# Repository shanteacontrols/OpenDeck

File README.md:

# OpenDeck

OpenDeck is a platform for building interactive control and sensing devices using MIDI and OSC. From USB MIDI DJ controllers and DAW control surfaces to Ethernet-connected OSC nodes, sensor interfaces and media installations, OpenDeck supports a wide range of hardware projects.

The main platform features:

* Browser-based configuration
* No firmware development required
* Hardware-independent - supports multiple MCU families and development boards
* MIDI and OSC support
* Extensible sensor support

The platform lets you focus on hardware and interaction design rather than tweaking and debugging firmware.

*Click the image below for a demo video of the [OpenDeck configurator](https://config.shanteacontrols.com)*

Configurator is available either [online](https://config.shanteacontrols.com) or [offline](https://github.com/shanteacontrols/OpenDeckUI/releases).

*Some of the devices built with OpenDeck*

## Peripherals

OpenDeck supports the following peripherals:

### Core I/O

* Buttons
* Encoders
* Single-color LEDs and other types of outputs such as relays or transistors
* Potentiometers
* FSRs (force-sensitive resistors)

### Displays

* [Nextion HMI](https://nextion.tech/) touchscreen displays
* [SSD1306 small OLED display](https://www.adafruit.com/product/326)

### Sensors

* [APDS-9960 proximity, light, RGB, and gesture sensor](https://www.adafruit.com/product/3595) - OSC only
* [CAP1188 8-Key Capacitive Touch Sensor](https://www.adafruit.com/product/1602) - OSC only
* [VL53L4CX time of flight distance sensor](https://www.adafruit.com/product/5425) - OSC only
* [VL53L5CX 8x8 time of flight distance sensor](https://www.sparkfun.com/sparkfun-qwiic-tof-imager-vl53l5cx.html) - OSC only
* [BNO085 9-DOF orientation IMU fusion sensor](https://www.adafruit.com/product/4754) - OSC only

Each sensor has specific configuration options such as smoothing, selectable event output etc.

## Features

OpenDeck provides extensive MIDI and OSC functionality:

* MIDI: sending of both 7-bit and 14-bit Non-Registered Parameter Numbers (NRPN), latching messages on buttons, various encoding modes for quadrature encoders, output control using MIDI In, configurable MIDI channels for each component individually, Bluetooth MIDI and more.
* OSC: Ethernet transport, configurable destinations, sensor data streaming, output control, automatic network discovery via mDNS, network-based configuration and firmware updates.

A detailed guide to all supported configurable features can be found [here](https://github.com/shanteacontrols/OpenDeck/wiki/Configurable-features).

If the feature you want isn't supported yet, don't feel discouraged. Open up a [discussion thread](https://github.com/shanteacontrols/OpenDeck/discussions) and let's talk about it.

## Official board

Currently, there is only one official board available to buy: the L variant, where "L" stands for "large". The board is available on [Lectronz store](https://lectronz.com/products/opendeck-l/).

This board is based on Raspberry Pi RP2040 microcontroller and features the following:

* 128 digital inputs
* 64 digital outputs
* 64 analog inputs
* DIN MIDI
* USB MIDI (USB C)
* Connector for touchscreen
* Connector for I2C OLED display
* Additional connectors with 3V+GND and 5V+GND connections

The L board doesn't have OSC support. It focuses on providing lots of I/O specifically for USB and DIN MIDI use-cases. OSC functionality is available on a number of supported Ethernet-enabled boards.

## Supported boards

The firmware supports various other boards, both small and large:

| Board | MIDI | OSC |
| --- | --- | --- |
| [Adafruit Grand Central M4 Express](https://www.adafruit.com/product/4064) | USB, DIN | No |
| [Adafruit Metro ESP32-S3](https://www.adafruit.com/product/5500) | USB, DIN | No |
| [Adafruit Metro ESP32-S3](https://www.adafruit.com/product/5500) + [W5500 Ethernet Shield](https://wiznet.io/products/open-source-hardware/w5500-ethernet-shield) | USB | Ethernet |
| [Adafruit Metro ESP32-S3](https://www.adafruit.com/product/5500) + [W6100 Ethernet Shield](https://wiznet.io/products/open-source-hardware/w6100-ethernet-shield) | USB | Ethernet |
| [Adafruit Metro RP2040](https://www.adafruit.com/product/5786) | USB, DIN | No |
| [Adafruit Metro RP2040](https://www.adafruit.com/product/5786) + [W5500 Ethernet Shield](https://wiznet.io/products/open-source-hardware/w5500-ethernet-shield) | USB | Ethernet |
| [Adafruit Metro RP2040](https://www.adafruit.com/product/5786) + [W6100 Ethernet Shield](https://wiznet.io/products/open-source-hardware/w6100-ethernet-shield) | USB | Ethernet |
| [Arduino Nano 33 BLE](https://store.arduino.cc/products/arduino-nano-33-ble) | USB, DIN, BLE | No |
| [LILYGO T-ETH Elite](https://lilygo.cc/products/t-eth-elite-1) | USB | Ethernet |
| [nRF52840 DK](https://www.nordicsemi.com/Products/Development-hardware/nrf52840-dk) | USB, DIN, BLE | No |
| [nRF5340 DK](https://www.nordicsemi.com/Products/Development-hardware/nrf5340-dk) | USB, DIN, BLE | No |
| [Olimex ESP32-POE](https://www.olimex.com/Products/IoT/ESP32/ESP32-POE/open-source-hardware) | No | Ethernet |
| [Raspberry Pi Pico](https://www.raspberrypi.com/products/raspberry-pi-pico/) | USB, DIN | No |
| [Raspberry Pi Pico 2](https://www.raspberrypi.com/products/raspberry-pi-pico-2/) | USB, DIN | No |
| [ST Discovery F407VG](https://www.st.com/en/evaluation-tools/stm32f4discovery.html) | USB, DIN | No |
| [ST Nucleo F767ZI](https://www.st.com/en/evaluation-tools/nucleo-f767zi.html) | DIN | Ethernet |
| [ST Nucleo H563ZI](https://www.st.com/en/evaluation-tools/nucleo-h563zi.html) | DIN | Ethernet |
| [ST Nucleo H753ZI](https://www.st.com/en/evaluation-tools/nucleo-h753zi.html) | DIN | Ethernet |
| [STM32F411 Black Pill V3+](https://www.adafruit.com/product/4877) with populated external flash | USB, DIN | No |
| [Teensy 4.0](https://www.pjrc.com/store/teensy40.html) | USB, DIN | No |
| [Teensy 4.1](https://www.pjrc.com/store/teensy41.html) | USB, DIN | No |
| [Waveshare Core405R](https://www.waveshare.com/core405r.htm) | USB, DIN | No |
| [Waveshare ESP32-S3-ETH](https://www.waveshare.com/esp32-s3-eth.htm) | USB | Ethernet |
| [W5500-EVB-Pico](https://docs.wiznet.io/Product/Open-Source-Hardware/w5500-evb-pico) | USB | Ethernet |
| [W5500-EVB-Pico2](https://docs.wiznet.io/Product/Open-Source-Hardware/w5500-evb-pico2) | USB, DIN | Ethernet |
| [W6100-EVB-Pico](https://docs.wiznet.io/Product/Open-Source-Hardware/w6100-evb-pico) | USB, DIN | Ethernet |
| [W6100-EVB-Pico2](https://docs.wiznet.io/Product/Open-Source-Hardware/w6100-evb-pico2) | USB, DIN | Ethernet |
| [wESP32](https://wesp32.com/) | No | Ethernet |

For more details on supported boards, check the [wiki page](https://github.com/shanteacontrols/OpenDeck/wiki). Support for custom boards [can also be added](https://github.com/shanteacontrols/OpenDeck/wiki/Creating-custom-board-variant).

## Documentation

Available on dedicated [Wiki section](https://github.com/shanteacontrols/OpenDeck/wiki/).

## Discussion

Need help? Want to show off your OpenDeck-based builds? Head over to [Discussions](https://github.com/shanteacontrols/OpenDeck/discussions)!

## License

OpenDeck source code is available under Apache License v2.0. Zephyr RTOS, which OpenDeck is built on top of, is also licensed under Apache License v2.0.

Third-party components with different licenses:

* `u8g2`: Two-clause BSD
* `vl53l4cx`: Three-clause BSD
* `vl53l5cx`: Three-clause BSD
* `zlibs`: MIT

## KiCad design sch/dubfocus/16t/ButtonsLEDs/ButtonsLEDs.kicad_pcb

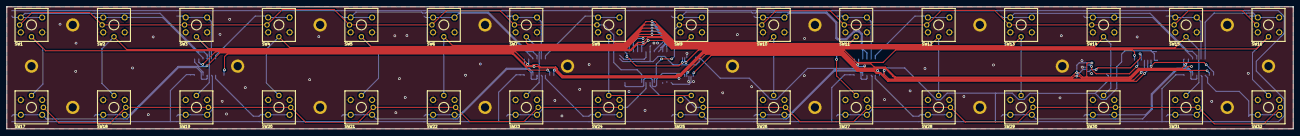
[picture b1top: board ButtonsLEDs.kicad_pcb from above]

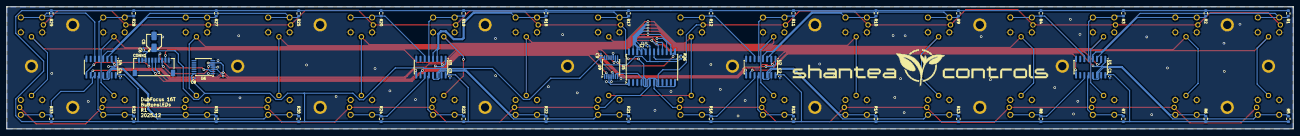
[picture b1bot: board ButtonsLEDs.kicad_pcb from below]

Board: 2 copper layers, 390.0 x 37.0 mm, 100 parts (50 on the bottom side), 61 nets.

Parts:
C1, C2, C3, C4, C6, C7, C8, C9: 100n; C_0402_1005Metric
C5: 10u; CP_Elec_4x5.4
CONN1: CONN_SM10B-SRSS-TB_JST
H1, H2, H3, H4, H5, H6, H7, H8, H9, H10, H11, H12, H13, H14, H15, H16, H17, H18: MountingHole_Pad; MountingHole_2.5mm_Pad
R1, R2, R3, R4, R5, R6, R7, R8, R9, R10, R11, R12, R13, R14, R15, R16, R17, R18, R19, R20, R21, R22, R23, R24, R25, R27, R28, R29, R30, R31, R32, R33: 4k7; R_0603_1608Metric
R26: 10k; R_0402_1005Metric
SW1, SW2, SW3, SW4, SW5, SW6, SW7, SW8, SW9, SW10, SW11, SW12, SW13, SW14, SW15, SW16, SW17, SW18, SW19, SW20, SW21, SW22, SW23, SW24, SW25, SW26, SW27, SW28, SW29, SW30, SW31, SW32: Omron-B3W-9
U1, U2, U3, U4: 74HC165; SOIC-16_3.9x9.9mm_P1.27mm
U5: MAX7219; SOIC-24W_7.5x15.4mm_P1.27mm
U6, U9: 74HCT125; TSSOP-14_4.4x5mm_P0.65mm

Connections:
+5V: C1.1, C2.1, C3.1, C4.1, C5.1, C6.1, C7.2, C8.2, C9.2, CONN1.2, CONN1.3, R1.2, R2.2, R3.2, R4.2, R5.2, R6.2, R7.2, R8.2, R9.2, R10.2, R11.2, R12.2, R13.2, R14.2, R15.2, R16.2, R17.2, R18.2, R19.2, R20.2, R21.2, R22.2, R23.2, R24.2, R25.2, R26.1, R27.2, R28.2, R29.2, R30.2, R31.2, R32.2, R33.2, U1.16 (VCC), U2.16 (VCC), U3.16 (VCC), U4.16 (VCC), U5.19 (V+), U6.14 (VCC), U9.14 (VCC)
/Buttons 1/BUTTON1: R1.1, SW1.1, SW1.2, U1.4 (D5)
/Buttons 1/BUTTON2: R2.1, SW2.1, SW2.2, U1.3 (D4)
/Buttons 1/BUTTON3: R3.1, SW3.1, SW3.2, U1.5 (D6)
/Buttons 1/BUTTON4: R4.1, SW4.1, SW4.2, U1.6 (D7)
/Buttons 1/BUTTON5: R5.1, SW17.1, SW17.2, U1.13 (D2)
/Buttons 1/BUTTON6: R6.1, SW18.1, SW18.2, U1.14 (D3)
/Buttons 1/BUTTON7: R7.1, SW19.1, SW19.2, U1.12 (D1)
/Buttons 1/BUTTON8: R8.1, SW20.1, SW20.2, U1.11 (D0)
/Buttons 2/BUTTON1: R9.1, SW5.1, SW5.2, U2.4 (D5)
/Buttons 2/BUTTON2: R10.1, SW6.1, SW6.2, U2.3 (D4)
/Buttons 2/BUTTON3: R11.1, SW7.1, SW7.2, U2.5 (D6)
/Buttons 2/BUTTON4: R12.1, SW8.1, SW8.2, U2.6 (D7)
/Buttons 2/BUTTON5: R13.1, SW21.1, SW21.2, U2.13 (D2)
/Buttons 2/BUTTON6: R14.1, SW22.1, SW22.2, U2.14 (D3)
/Buttons 2/BUTTON7: R15.1, SW23.1, SW23.2, U2.12 (D1)
/Buttons 2/BUTTON8: R16.1, SW24.1, SW24.2, U2.11 (D0)
/Buttons 3/BUTTON1: R17.1, SW9.1, SW9.2, U3.4 (D5)
/Buttons 3/BUTTON2: R18.1, SW10.1, SW10.2, U3.3 (D4)
/Buttons 3/BUTTON3: R19.1, SW11.1, SW11.2, U3.5 (D6)
/Buttons 3/BUTTON4: R20.1, SW12.1, SW12.2, U3.6 (D7)
/Buttons 3/BUTTON5: R21.1, SW25.1, SW25.2, U3.13 (D2)
/Buttons 3/BUTTON6: R22.1, SW26.1, SW26.2, U3.14 (D3)
/Buttons 3/BUTTON7: R23.1, SW27.1, SW27.2, U3.12 (D1)
/Buttons 3/BUTTON8: R24.1, SW28.1, SW28.2, U3.11 (D0)
/Buttons 4/BUTTON1: R25.1, SW13.1, SW13.2, U4.4 (D5)
/Buttons 4/BUTTON2: R27.1, SW14.1, SW14.2, U4.3 (D4)
/Buttons 4/BUTTON3: R28.1, SW15.1, SW15.2, U4.5 (D6)
/Buttons 4/BUTTON4: R29.1, SW16.1, SW16.2, U4.6 (D7)
/Buttons 4/BUTTON5: R30.1, SW29.1, SW29.2, U4.13 (D2)
/Buttons 4/BUTTON6: R31.1, SW30.1, SW30.2, U4.14 (D3)
/Buttons 4/BUTTON7: R32.1, SW31.1, SW31.2, U4.12 (D1)
/Buttons 4/BUTTON8: R33.1, SW32.1, SW32.2, U4.11 (D0)
/LEDs/LED_COLUMN_1: SW1.- (K), SW2.- (K), SW3.- (K), SW4.- (K), SW5.- (K), SW6.- (K), SW7.- (K), SW8.- (K), U5.8 (DIG_7)
/LEDs/LED_COLUMN_2: SW17.- (K), SW18.- (K), SW19.- (K), SW20.- (K), SW21.- (K), SW22.- (K), SW23.- (K), SW24.- (K), U5.7 (DIG_3)
/LEDs/LED_COLUMN_3: SW9.- (K), SW10.- (K), SW11.- (K), SW12.- (K), SW13.- (K), SW14.- (K), SW15.- (K), SW16.- (K), U5.5 (DIG_6)
/LEDs/LED_COLUMN_4: SW25.- (K), SW26.- (K), SW27.- (K), SW28.- (K), SW29.- (K), SW30.- (K), SW31.- (K), SW32.- (K), U5.6 (DIG_2)
/LEDs/LED_ROW_1: SW1.+ (A), SW16.+ (A), SW17.+ (A), SW32.+ (A), U5.17 (SEG_G)
/LEDs/LED_ROW_2: SW2.+ (A), SW15.+ (A), SW18.+ (A), SW31.+ (A), U5.16 (SEG_B)
/LEDs/LED_ROW_3: SW3.+ (A), SW14.+ (A), SW19.+ (A), SW30.+ (A), U5.15 (SEG_F)
/LEDs/LED_ROW_4: SW4.+ (A), SW13.+ (A), SW20.+ (A), SW29.+ (A), U5.14 (SEG_A)
/LEDs/LED_ROW_5: SW5.+ (A), SW12.+ (A), SW21.+ (A), SW28.+ (A), U5.20 (SEG_C)
/LEDs/LED_ROW_6: SW6.+ (A), SW11.+ (A), SW22.+ (A), SW27.+ (A), U5.21 (SEG_E)
/LEDs/LED_ROW_7: SW7.+ (A), SW10.+ (A), SW23.+ (A), SW26.+ (A), U5.22 (SEG_DP)
/LEDs/LED_ROW_8: SW8.+ (A), SW9.+ (A), SW24.+ (A), SW25.+ (A), U5.23 (SEG_D)
/MAX7219_CLK_3V: CONN1.9, U9.9 (3A)
/MAX7219_CLK_5V: U5.13 (CLK), U9.8 (3Y)
/MAX7219_DIN_3V: CONN1.5, U9.2 (1A)
/MAX7219_DIN_5V: U5.1 (DIN), U9.3 (1Y)
/MAX7219_LOAD_3V: CONN1.6, U9.5 (2A)
/MAX7219_LOAD_5V: U5.12 (LOAD), U9.6 (2Y)
/SR_IN_CLOCK_3V: CONN1.8, U6.5 (2A)
/SR_IN_CLOCK_5V: U1.2 (CP), U2.2 (CP), U3.2 (CP), U4.2 (CP), U6.6 (2Y)
/SR_IN_DAISY_OUT_1: U3.9 (Q7), U4.10 (DS)
/SR_IN_DAISY_OUT_2: U2.9 (Q7), U3.10 (DS)
/SR_IN_DAISY_OUT_3: U1.9 (Q7), U2.10 (DS)
/SR_IN_DATA: CONN1.4, U4.9 (Q7)
/SR_IN_LATCH_3V: CONN1.7, U6.2 (1A)
/SR_IN_LATCH_5V: U1.1 (~PL), U2.1 (~PL), U3.1 (~PL), U4.1 (~PL), U6.3 (1Y)
GND: C1.2, C2.2, C3.2, C4.2, C5.2, C6.2, C7.1, C8.1, C9.1, CONN1.1, CONN1.10, CONN1.S1, CONN1.S2, H1.1, H2.1, H3.1, H4.1, H5.1, H6.1, H7.1, H8.1, H9.1, H10.1, H11.1, H12.1, H13.1, H14.1, H15.1, H16.1, H17.1, H18.1, SW1.3, SW1.4, SW2.3, SW2.4, SW3.3, SW3.4, SW4.3, SW4.4, SW5.3, SW5.4, SW6.3, SW6.4, SW7.3, SW7.4, SW8.3, SW8.4, SW9.3, SW9.4, SW10.3, SW10.4, SW11.3, SW11.4, SW12.3, SW12.4, SW13.3, SW13.4, SW14.3, SW14.4, SW15.3, SW15.4, SW16.3, SW16.4, SW17.3, SW17.4, SW18.3, SW18.4, SW19.3, SW19.4, SW20.3, SW20.4, SW21.3, SW21.4, SW22.3, SW22.4, SW23.3, SW23.4, SW24.3, SW24.4, SW25.3, SW25.4, SW26.3, SW26.4, SW27.3, SW27.4, SW28.3, SW28.4, SW29.3, SW29.4, SW30.3, SW30.4, SW31.3, SW31.4, SW32.3, SW32.4, U1.8 (GND), U1.15 (~CE), U2.8 (GND), U2.15 (~CE), U3.8 (GND), U3.15 (~CE), U4.8 (GND), U4.15 (~CE), U5.4 (GND), U5.9 (GND), U6.1 (1~OE), U6.4 (2~OE), U6.7 (GND), U9.1 (1~OE), U9.4 (2~OE), U9.7 (GND), U9.10 (3~OE)
unnamed: R26.2, U5.18 (ISET)

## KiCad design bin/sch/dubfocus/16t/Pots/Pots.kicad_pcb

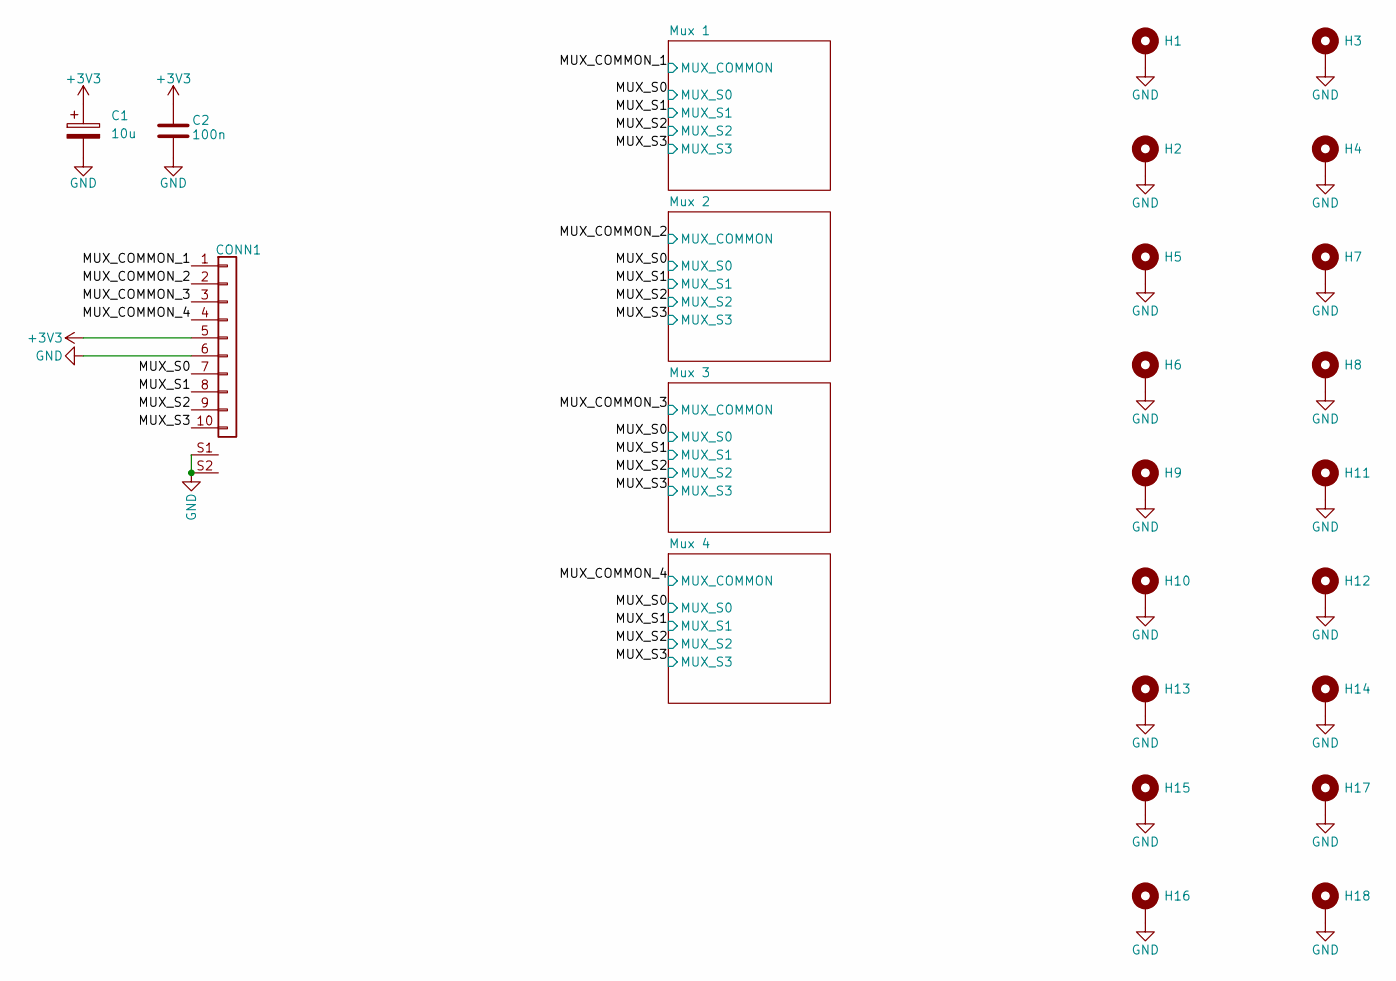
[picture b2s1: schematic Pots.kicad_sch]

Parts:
C1: 10u; CP_Elec_4x5.4; LCSC C4747968
C2: 100n; C_0402_1005Metric; LCSC C1525
CONN1: CONN_SM10B-SRSS-TB_JST; LCSC C160409
H1, H2, H3, H4, H5, H6, H7, H8, H9, H10, H11, H12, H13, H14, H15, H16, H17, H18: MountingHole_Pad; MountingHole_2.5mm_Pad

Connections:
+3V3: C1.1, C2.1, CONN1.5; also elsewhere on the board
/MUX_COMMON_1: CONN1.1; also elsewhere on the board
/MUX_COMMON_2: CONN1.2; also elsewhere on the board
/MUX_COMMON_3: CONN1.3; also elsewhere on the board
/MUX_COMMON_4: CONN1.4; also elsewhere on the board
/MUX_S0: CONN1.7; also elsewhere on the board
/MUX_S1: CONN1.8; also elsewhere on the board
/MUX_S2: CONN1.9; also elsewhere on the board
/MUX_S3: CONN1.10; also elsewhere on the board
GND: C1.2, C2.2, CONN1.6, CONN1.S1, CONN1.S2, H1.1, H2.1, H3.1, H4.1, H5.1, H6.1, H7.1, H8.1, H9.1, H10.1, H11.1, H12.1, H13.1, H14.1, H15.1, H16.1, H17.1, H18.1; also elsewhere on the board

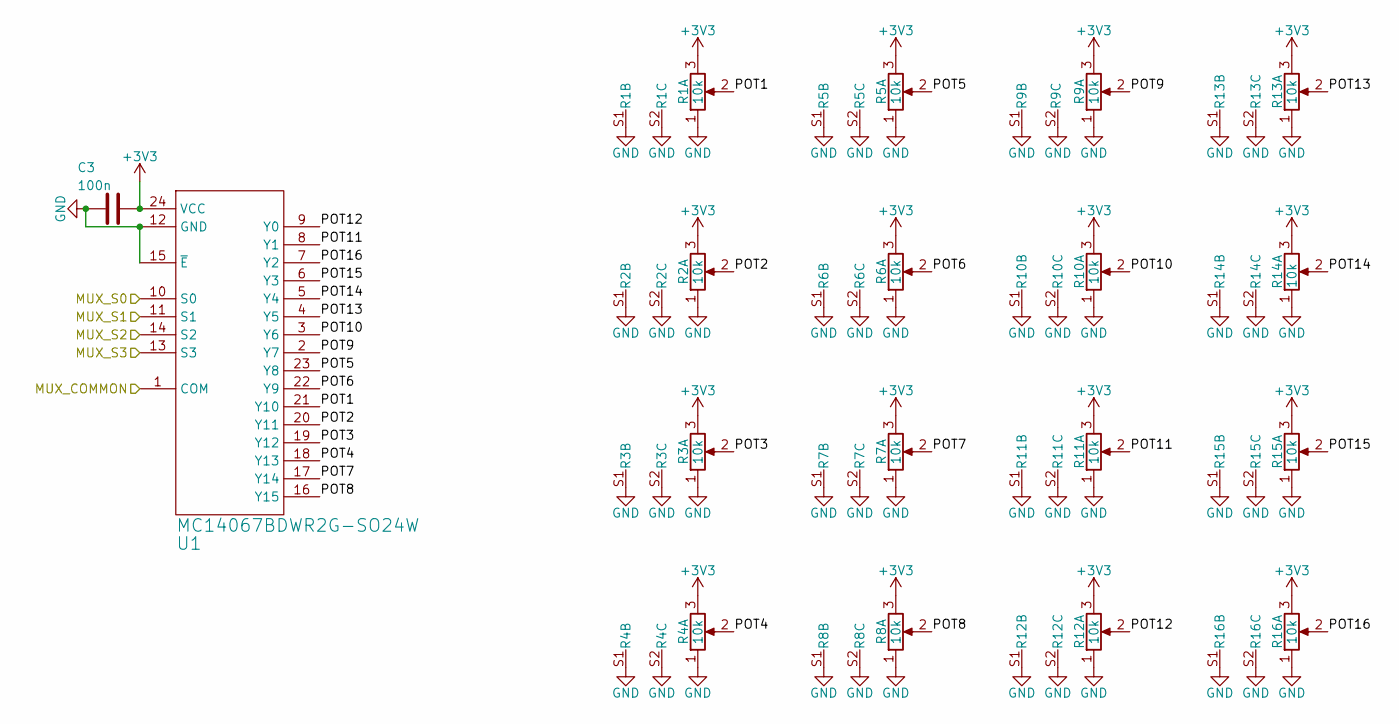
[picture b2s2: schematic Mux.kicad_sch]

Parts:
C3: 100n; C_0402_1005Metric; LCSC C1525
R1, R2, R3, R4, R5, R6, R7, R8, R9, R10, R11, R12, R13, R14, R15, R16: 10k; PTV09A-4025F-B103; LCSC C7262626
U1: MC14067BDWR2G-SO24W; SOIC-24W_7.5x15.4mm_P1.27mm; LCSC C555478

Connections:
+3V3: C3.2, R1.3, R2.3, R3.3, R4.3, R5.3, R6.3, R7.3, R8.3, R9.3, R10.3, R11.3, R12.3, R13.3, R14.3, R15.3, R16.3, U1.24 (VCC); also elsewhere on the board
/MUX_COMMON_1: U1.1 (COM); also elsewhere on the board
/MUX_S0: U1.10 (S0); also elsewhere on the board
/MUX_S1: U1.11 (S1); also elsewhere on the board
/MUX_S2: U1.14 (S2); also elsewhere on the board
/MUX_S3: U1.13 (S3); also elsewhere on the board
/Mux 1/POT1: R1.2, U1.21 (Y10)
/Mux 1/POT2: R2.2, U1.20 (Y11)
/Mux 1/POT3: R3.2, U1.19 (Y12)
/Mux 1/POT4: R4.2, U1.18 (Y13)
/Mux 1/POT5: R5.2, U1.23 (Y8)
/Mux 1/POT6: R6.2, U1.22 (Y9)
/Mux 1/POT7: R7.2, U1.17 (Y14)
/Mux 1/POT8: R8.2, U1.16 (Y15)
/Mux 1/POT9: R9.2, U1.2 (Y7)
/Mux 1/POT10: R10.2, U1.3 (Y6)
/Mux 1/POT11: R11.2, U1.8 (Y1)
/Mux 1/POT12: R12.2, U1.9 (Y0)
/Mux 1/POT13: R13.2, U1.4 (Y5)
/Mux 1/POT14: R14.2, U1.5 (Y4)
/Mux 1/POT15: R15.2, U1.6 (Y3)
/Mux 1/POT16: R16.2, U1.7 (Y2)
GND: C3.1, R1.1, R1.S1, R1.S2, R2.1, R2.S1, R2.S2, R3.1, R3.S1, R3.S2, R4.1, R4.S1, R4.S2, R5.1, R5.S1, R5.S2, R6.1, R6.S1, R6.S2, R7.1, R7.S1, R7.S2, R8.1, R8.S1, R8.S2, R9.1, R9.S1, R9.S2, R10.1, R10.S1, R10.S2, R11.1, R11.S1, R11.S2, R12.1, R12.S1, R12.S2, R13.1, R13.S1, R13.S2, R14.1, R14.S1, R14.S2, R15.1, R15.S1, R15.S2, R16.1, R16.S1, R16.S2, U1.12 (GND), U1.15 (~E); also elsewhere on the board

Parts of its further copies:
C4, C5, C6: 100n; C_0402_1005Metric; LCSC C1525
R17, R18, R19, R20, R21, R22, R23, R24, R25, R26, R27, R28, R29, R30, R31, R32, R33, R34, R35, R36, R37, R38, R39, R40, R41, R42, R43, R44, R45, R46, R47, R48, R49, R50, R51, R52, R53, R54, R55, R56, R57, R58, R59, R60, R61, R62, R63, R64: 10k; PTV09A-4025F-B103; LCSC C7262626
U2, U3, U4: MC14067BDWR2G-SO24W; SOIC-24W_7.5x15.4mm_P1.27mm; LCSC C555478

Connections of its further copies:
+3V3: C4.2, C5.2, C6.2, R17.3, R18.3, R19.3, R20.3, R21.3, R22.3, R23.3, R24.3, R25.3, R26.3, R27.3, R28.3, R29.3, R30.3, R31.3, R32.3, R33.3, R34.3, R35.3, R36.3, R37.3, R38.3, R39.3, R40.3, R41.3, R42.3, R43.3, R44.3, R45.3, R46.3, R47.3, R48.3, R49.3, R50.3, R51.3, R52.3, R53.3, R54.3, R55.3, R56.3, R57.3, R58.3, R59.3, R60.3, R61.3, R62.3, R63.3, R64.3, U2.24 (VCC), U3.24 (VCC), U4.24 (VCC); also elsewhere on the board
/MUX_COMMON_2: U2.1 (COM); also elsewhere on the board
/MUX_COMMON_3: U3.1 (COM); also elsewhere on the board
/MUX_COMMON_4: U4.1 (COM); also elsewhere on the board
/MUX_S0: U2.10 (S0), U3.10 (S0), U4.10 (S0); also elsewhere on the board
/MUX_S1: U2.11 (S1), U3.11 (S1), U4.11 (S1); also elsewhere on the board
/MUX_S2: U2.14 (S2), U3.14 (S2), U4.14 (S2); also elsewhere on the board
/MUX_S3: U2.13 (S3), U3.13 (S3), U4.13 (S3); also elsewhere on the board
/Mux 2/POT1: R17.2, U2.21 (Y10)
/Mux 2/POT2: R18.2, U2.20 (Y11)
/Mux 2/POT3: R19.2, U2.19 (Y12)
/Mux 2/POT4: R20.2, U2.18 (Y13)
/Mux 2/POT5: R21.2, U2.23 (Y8)
/Mux 2/POT6: R22.2, U2.22 (Y9)
/Mux 2/POT7: R23.2, U2.17 (Y14)
/Mux 2/POT8: R24.2, U2.16 (Y15)
/Mux 2/POT9: R25.2, U2.2 (Y7)
/Mux 2/POT10: R26.2, U2.3 (Y6)
/Mux 2/POT11: R27.2, U2.8 (Y1)
/Mux 2/POT12: R28.2, U2.9 (Y0)
/Mux 2/POT13: R29.2, U2.4 (Y5)
/Mux 2/POT14: R30.2, U2.5 (Y4)
/Mux 2/POT15: R31.2, U2.6 (Y3)
/Mux 2/POT16: R32.2, U2.7 (Y2)
/Mux 3/POT1: R33.2, U3.21 (Y10)
/Mux 3/POT2: R34.2, U3.20 (Y11)
/Mux 3/POT3: R35.2, U3.19 (Y12)
/Mux 3/POT4: R36.2, U3.18 (Y13)
/Mux 3/POT5: R37.2, U3.23 (Y8)
/Mux 3/POT6: R38.2, U3.22 (Y9)
/Mux 3/POT7: R39.2, U3.17 (Y14)
/Mux 3/POT8: R40.2, U3.16 (Y15)
/Mux 3/POT9: R41.2, U3.2 (Y7)
/Mux 3/POT10: R42.2, U3.3 (Y6)
/Mux 3/POT11: R43.2, U3.8 (Y1)
/Mux 3/POT12: R44.2, U3.9 (Y0)
/Mux 3/POT13: R45.2, U3.4 (Y5)
/Mux 3/POT14: R46.2, U3.5 (Y4)
/Mux 3/POT15: R47.2, U3.6 (Y3)
/Mux 3/POT16: R48.2, U3.7 (Y2)
/Mux 4/POT1: R49.2, U4.21 (Y10)
/Mux 4/POT2: R50.2, U4.20 (Y11)
/Mux 4/POT3: R51.2, U4.19 (Y12)
/Mux 4/POT4: R52.2, U4.18 (Y13)
/Mux 4/POT5: R53.2, U4.23 (Y8)
/Mux 4/POT6: R54.2, U4.22 (Y9)
/Mux 4/POT7: R55.2, U4.17 (Y14)
/Mux 4/POT8: R56.2, U4.16 (Y15)
/Mux 4/POT9: R57.2, U4.2 (Y7)
/Mux 4/POT10: R58.2, U4.3 (Y6)
/Mux 4/POT11: R59.2, U4.8 (Y1)
/Mux 4/POT12: R60.2, U4.9 (Y0)
/Mux 4/POT13: R61.2, U4.4 (Y5)
/Mux 4/POT14: R62.2, U4.5 (Y4)
/Mux 4/POT15: R63.2, U4.6 (Y3)
/Mux 4/POT16: R64.2, U4.7 (Y2)
GND: C4.1, C5.1, C6.1, R17.1, R17.S1, R17.S2, R18.1, R18.S1, R18.S2, R19.1, R19.S1, R19.S2, R20.1, R20.S1, R20.S2, R21.1, R21.S1, R21.S2, R22.1, R22.S1, R22.S2, R23.1, R23.S1, R23.S2, R24.1, R24.S1, R24.S2, R25.1, R25.S1, R25.S2, R26.1, R26.S1, R26.S2, R27.1, R27.S1, R27.S2, R28.1, R28.S1, R28.S2, R29.1, R29.S1, R29.S2, R30.1, R30.S1, R30.S2, R31.1, R31.S1, R31.S2, R32.1, R32.S1, R32.S2, R33.1, R33.S1, R33.S2, R34.1, R34.S1, R34.S2, R35.1, R35.S1, R35.S2, R36.1, R36.S1, R36.S2, R37.1, R37.S1, R37.S2, R38.1, R38.S1, R38.S2, R39.1, R39.S1, R39.S2, R40.1, R40.S1, R40.S2, R41.1, R41.S1, R41.S2, R42.1, R42.S1, R42.S2, R43.1, R43.S1, R43.S2, R44.1, R44.S1, R44.S2, R45.1, R45.S1, R45.S2, R46.1, R46.S1, R46.S2, R47.1, R47.S1, R47.S2, R48.1, R48.S1, R48.S2, R49.1, R49.S1, R49.S2, R50.1, R50.S1, R50.S2, R51.1, R51.S1, R51.S2, R52.1, R52.S1, R52.S2, R53.1, R53.S1, R53.S2, R54.1, R54.S1, R54.S2, R55.1, R55.S1, R55.S2, R56.1, R56.S1, R56.S2, R57.1, R57.S1, R57.S2, R58.1, R58.S1, R58.S2, R59.1, R59.S1, R59.S2, R60.1, R60.S1, R60.S2, R61.1, R61.S1, R61.S2, R62.1, R62.S1, R62.S2, R63.1, R63.S1, R63.S2, R64.1, R64.S1, R64.S2, U2.12 (GND), U2.15 (~E), U3.12 (GND), U3.15 (~E), U4.12 (GND), U4.15 (~E); also elsewhere on the board

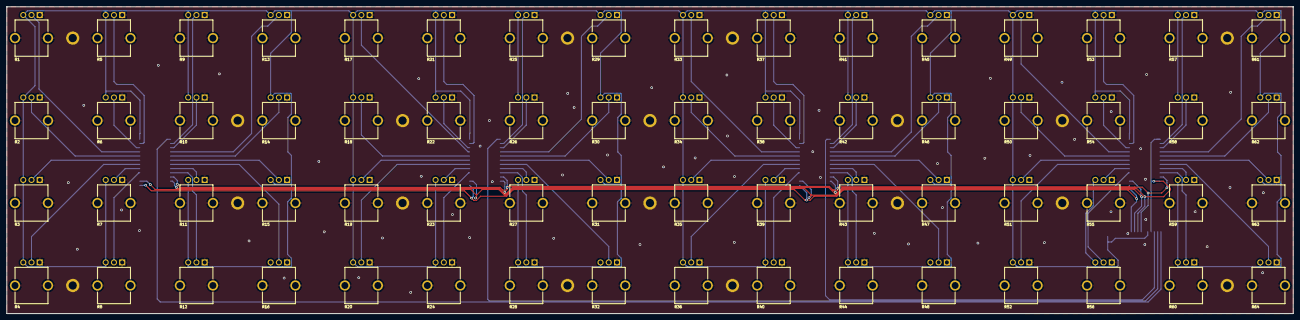
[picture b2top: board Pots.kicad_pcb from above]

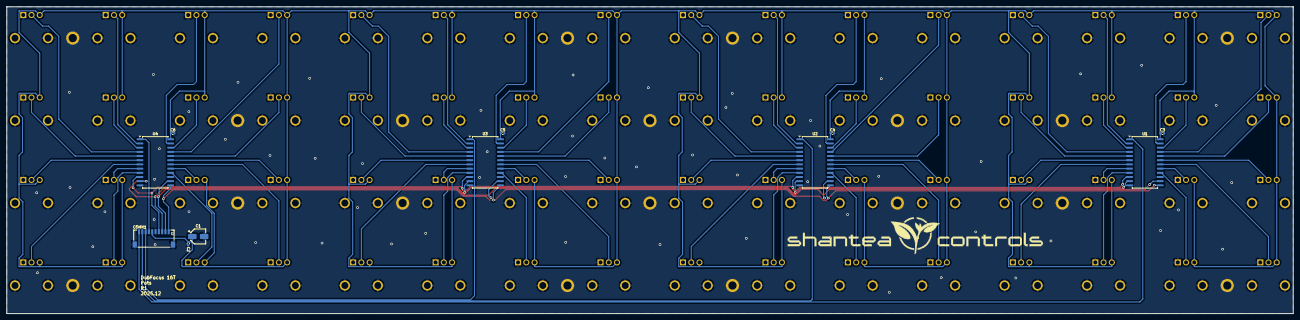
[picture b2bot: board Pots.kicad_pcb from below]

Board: 2 copper layers, 390.0 x 93.0 mm, 93 parts (11 on the bottom side), 74 nets.

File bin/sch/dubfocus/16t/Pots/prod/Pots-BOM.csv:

Comment,Designator,Footprint,LCSC
"10u","C1","Capacitor_SMD:CP_Elec_4x5.4","C4747968"
"100n","C2,C3,C4,C5,C6","Capacitor_SMD:C_0402_1005Metric","C1525"
"~","CONN1","Igor:CONN_SM10B-SRSS-TB_JST","C160409"
"10k","R1,R2,R3,R4,R5,R6,R7,R8,R9,R10,R11,R12,R13,R14,R15,R16,R17,R18,R19,R20,R21,R22,R23,R24,R25,R26,R27,R28,R29,R30,R31,R32,R33,R34,R35,R36,R37,R38,R39,R40,R41,R42,R43,R44,R45,R46,R47,R48,R49,R50,R51,R52,R53,R54,R55,R56,R57,R58,R59,R60,R61,R62,R63,R64","Igor:PTV09A-4025F-B103","C7262626"
"MC14067BDWR2G-SO24W","U1,U2,U3,U4","Package_SO:SOIC-24W_7.5x15.4mm_P1.27mm","C555478"

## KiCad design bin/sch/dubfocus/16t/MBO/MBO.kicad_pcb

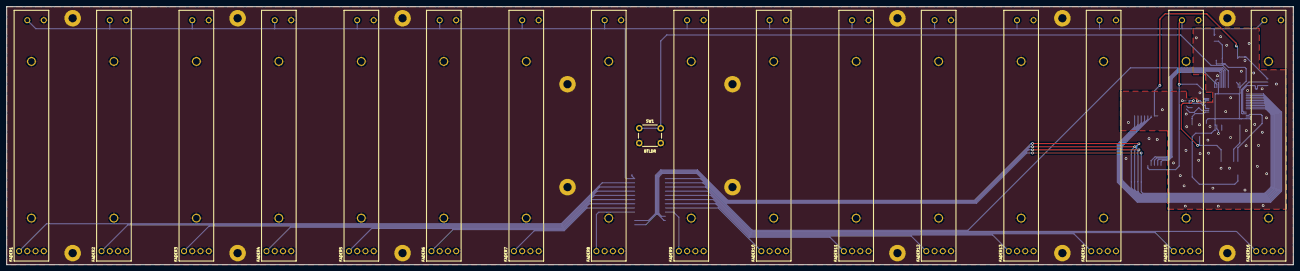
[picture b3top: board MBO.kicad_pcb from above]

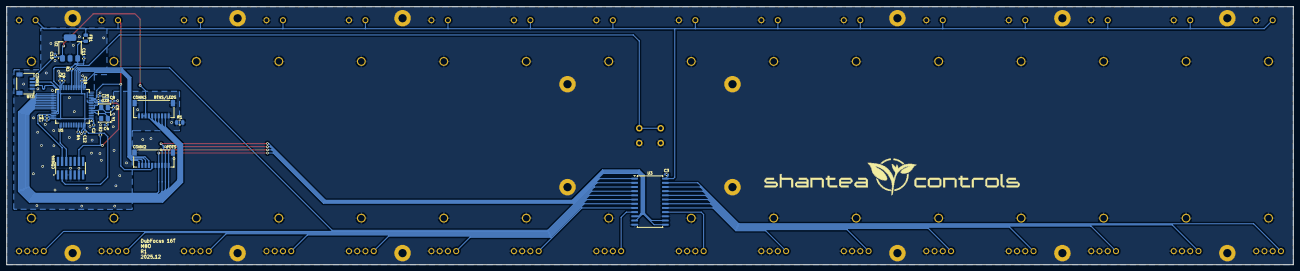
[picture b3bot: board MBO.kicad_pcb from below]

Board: 2 copper layers, 390.0 x 78.2 mm, 61 parts (28 on the bottom side), 47 nets.

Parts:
C1, C9: 2.2u; C_0402_1005Metric
C2, C3, C6, C7, C8, C12, C19, C25: 100n; C_0402_1005Metric
C4, C5: 18p; C_0402_1005Metric
C10, C11: 4.7u; C_0402_1005Metric
C23: 1u; C_0402_1005Metric
CONN1: Conn_01x04; CONN_SM04B-SRSS-TB_JST
CONN2, CONN3: PINHD-1X10-FFC-1MM-Z; CONN_SM10B-SRSS-TB_JST
CONN4: Conn_ST_STDC14; SAMTEC_FTSH-107-01-L-DV-K
FADER1, FADER2, FADER3, FADER4, FADER5, FADER6, FADER7, FADER8, FADER9, FADER10, FADER11, FADER12, FADER13, FADER14, FADER15, FADER16: RS6011SP6003; RS6011_P
FB1: 30R@100MHz; R_0805_2012Metric
H1, H2, H3, H4, H5, H6, H7, H8, H9, H10, H11, H12, H13, H14, H15, H16: MountingHole_Pad; MountingHole_2.5mm_Pad
R1: 0; R_0805_2012Metric
R2, R3, R4: 5.1k; R_0402_1005Metric
SW1: SW_PUSH_6mm
U2: MCP1825S; SOT-223
U3: MC14067BDWR2G-SO24W; SOIC-24W_7.5x15.4mm_P1.27mm
U5: STM32F405RGTx; LQFP-64_10x10mm_P0.5mm
Y1: 8MHz; Crystal_SMD_5032-4Pin_5.0x3.2mm

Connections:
+3.3VADC: C3.2, C23.1, C25.1, CONN2.6, FADER1.3, FADER2.3, FADER3.3, FADER4.3, FADER5.3, FADER6.3, FADER7.3, FADER8.3, FADER9.3, FADER10.3, FADER11.3, FADER12.3, FADER13.3, FADER14.3, FADER15.3, FADER16.3, FB1.2, U3.24 (VCC), U5.13 (VDDA)
+3V3: C2.2, C6.2, C7.2, C11.1, C12.2, C19.2, CONN4.3 (VCC), FB1.1, R2.2, R3.2, U2.3 (VO), U5.1 (VBAT), U5.19 (VDD), U5.32 (VDD), U5.48 (VDD), U5.64 (VDD)
+5V: C10.1, CONN1.1, CONN3.8, CONN3.9, U2.1 (VI)
/MAX7219_CLK: CONN3.2, U5.33 (PB12)
/MAX7219_DIN: CONN3.6, U5.37 (PC6)
/MAX7219_LOAD: CONN3.5, U5.36 (PB15)
/MCU/BOOT0: R4.2, U5.60 (BOOT0)
/MCU/BTLDR_BUTTON: R3.1, SW1.1 (A), U5.25 (PC5)
/MCU/OSC_IN: C4.1, U5.5 (PH0), Y1.1
/MCU/OSC_OUT: C5.2, U5.6 (PH1), Y1.3
/MUX_COMMON_1: CONN2.10, U5.17 (PA3)
/MUX_COMMON_2: CONN2.9, U5.20 (PA4)
/MUX_COMMON_3: CONN2.8, U5.21 (PA5)
/MUX_COMMON_4: CONN2.7, U5.22 (PA6)
/MUX_COMMON_5: U3.1 (COM), U5.23 (PA7)
/MUX_S0: CONN2.4, U3.10 (S0), U5.42 (PA9)
/MUX_S1: CONN2.3, U3.11 (S1), U5.41 (PA8)
/MUX_S2: CONN2.2, U3.14 (S2), U5.40 (PC9)
/MUX_S3: CONN2.1, U3.13 (S3), U5.39 (PC8)
/NRST: C8.2, CONN4.12 (~RST), R2.1, U5.7 (NRST)
/Pots/FADER1: FADER1.2, U3.23 (Y8)
/Pots/FADER2: FADER2.2, U3.22 (Y9)
/Pots/FADER3: FADER3.2, U3.21 (Y10)
/Pots/FADER4: FADER4.2, U3.20 (Y11)
/Pots/FADER5: FADER5.2, U3.19 (Y12)
/Pots/FADER6: FADER6.2, U3.18 (Y13)
/Pots/FADER7: FADER7.2, U3.17 (Y14)
/Pots/FADER8: FADER8.2, U3.16 (Y15)
/Pots/FADER9: FADER9.2, U3.9 (Y0)
/Pots/FADER10: FADER10.2, U3.8 (Y1)
/Pots/FADER11: FADER11.2, U3.7 (Y2)
/Pots/FADER12: FADER12.2, U3.6 (Y3)
/Pots/FADER13: FADER13.2, U3.5 (Y4)
/Pots/FADER14: FADER14.2, U3.4 (Y5)
/Pots/FADER15: FADER15.2, U3.3 (Y6)
/Pots/FADER16: FADER16.2, U3.2 (Y7)
/SR_IN_CLOCK: CONN3.3, U5.34 (PB13)
/SR_IN_DATA: CONN3.7, U5.38 (PC7)
/SR_IN_LATCH: CONN3.4, U5.35 (PB14)
/SWDCLK: CONN4.6 (JCLK/SWCLK), U5.49 (PA14)
/SWDIO: CONN4.4 (JTMS/SWDIO), U5.46 (PA13)
/USB_DM: CONN1.3, U5.44 (PA11)
/USB_DP: CONN1.2, U5.45 (PA12)
GND: C1.1, C2.1, C4.2, C5.1, C6.1, C7.1, C8.1, C9.1, C10.2, C11.2, C12.1, C19.1, CONN1.4, CONN1.S1, CONN1.S2, CONN3.1, CONN3.10, CONN3.S1, CONN3.S2, CONN4.5 (GND), CONN4.7 (GND), CONN4.11 (GNDDetect), R1.1, R4.1, U2.2 (GND), U2.4 (GND), U5.18 (VSS), U5.63 (VSS), Y1.2, Y1.4
GNDA: C3.1, C23.2, C25.2, CONN2.5, CONN2.S1, CONN2.S2, FADER1.1, FADER1.S1, FADER1.S2, FADER1.S3, FADER1.S4, FADER1.S5, FADER2.1, FADER2.S1, FADER2.S2, FADER2.S3, FADER2.S4, FADER2.S5, FADER3.1, FADER3.S1, FADER3.S2, FADER3.S3, FADER3.S4, FADER3.S5, FADER4.1, FADER4.S1, FADER4.S2, FADER4.S3, FADER4.S4, FADER4.S5, FADER5.1, FADER5.S1, FADER5.S2, FADER5.S3, FADER5.S4, FADER5.S5, FADER6.1, FADER6.S1, FADER6.S2, FADER6.S3, FADER6.S4, FADER6.S5, FADER7.1, FADER7.S1, FADER7.S2, FADER7.S3, FADER7.S4, FADER7.S5, FADER8.1, FADER8.S1, FADER8.S2, FADER8.S3, FADER8.S4, FADER8.S5, FADER9.1, FADER9.S1, FADER9.S2, FADER9.S3, FADER9.S4, FADER9.S5, FADER10.1, FADER10.S1, FADER10.S2, FADER10.S3, FADER10.S4, FADER10.S5, FADER11.1, FADER11.S1, FADER11.S2, FADER11.S3, FADER11.S4, FADER11.S5, FADER12.1, FADER12.S1, FADER12.S2, FADER12.S3, FADER12.S4, FADER12.S5, FADER13.1, FADER13.S1, FADER13.S2, FADER13.S3, FADER13.S4, FADER13.S5, FADER14.1, FADER14.S1, FADER14.S2, FADER14.S3, FADER14.S4, FADER14.S5, FADER15.1, FADER15.S1, FADER15.S2, FADER15.S3, FADER15.S4, FADER15.S5, FADER16.1, FADER16.S1, FADER16.S2, FADER16.S3, FADER16.S4, FADER16.S5, H1.1, H2.1, H3.1, H4.1, H5.1, H6.1, H7.1, H8.1, H9.1, H10.1, H11.1, H12.1, H13.1, H14.1, H15.1, H16.1, R1.2, SW1.2 (B), U3.12 (GND), U3.15 (~E), U5.12 (VSSA)
unnamed: C9.2, U5.31 (VCAP_1)
unnamed: C1.2, U5.47 (VCAP_2)

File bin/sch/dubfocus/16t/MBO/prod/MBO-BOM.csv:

Comment,Designator,Footprint,LCSC
"2.2u","C1,C9","Capacitor_SMD:C_0402_1005Metric","C12530"
"4.7u","C10,C11","Capacitor_SMD:C_0402_1005Metric","C23687"
"100n","C2,C3,C6,C7,C8,C12,C19,C25","Capacitor_SMD:C_0402_1005Metric","C1525"
"1u","C23","Capacitor_SMD:C_0402_1005Metric","C307413"
"18p","C4,C5","Capacitor_SMD:C_0402_1005Metric","C541431"
"Conn_01x04","CONN1","Igor:CONN_SM04B-SRSS-TB_JST","C160404"
"PINHD-1X10-FFC-1MM-Z","CONN2,CONN3","Igor:CONN_SM10B-SRSS-TB_JST","C160409"
"Conn_ST_STDC14","CONN4","Igor:SAMTEC_FTSH-107-01-L-DV-K","C5307809"
"RS6011SP6003","FADER1,FADER2,FADER3,FADER4,FADER5,FADER6,FADER7,FADER8,FADER9,FADER10,FADER11,FADER12,FADER13,FADER14,FADER15,FADER16","Igor:RS6011_P","C370993"
"30R@100MHz","FB1","Resistor_SMD:R_0805_2012Metric","C16903"
"0","R1","Resistor_SMD:R_0805_2012Metric","C2074916"
"5.1k","R2,R3,R4","Resistor_SMD:R_0402_1005Metric","C25905"
"~","SW1","Button_Switch_THT:SW_PUSH_6mm","C13828"
"MCP1825S","U2","Package_TO_SOT_SMD:SOT-223","C148031"
"MC14067BDWR2G-SO24W","U3","Package_SO:SOIC-24W_7.5x15.4mm_P1.27mm","C555478"
"STM32F405RGTx","U5","Package_QFP:LQFP-64_10x10mm_P0.5mm","C15742"
"8MHz","Y1","Crystal:Crystal_SMD_5032-4Pin_5.0x3.2mm","C2901620"
